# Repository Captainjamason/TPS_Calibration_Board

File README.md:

# TPS_Calibration_Board
WIP...          Copyright JPD/Davis Tuning, 2025.

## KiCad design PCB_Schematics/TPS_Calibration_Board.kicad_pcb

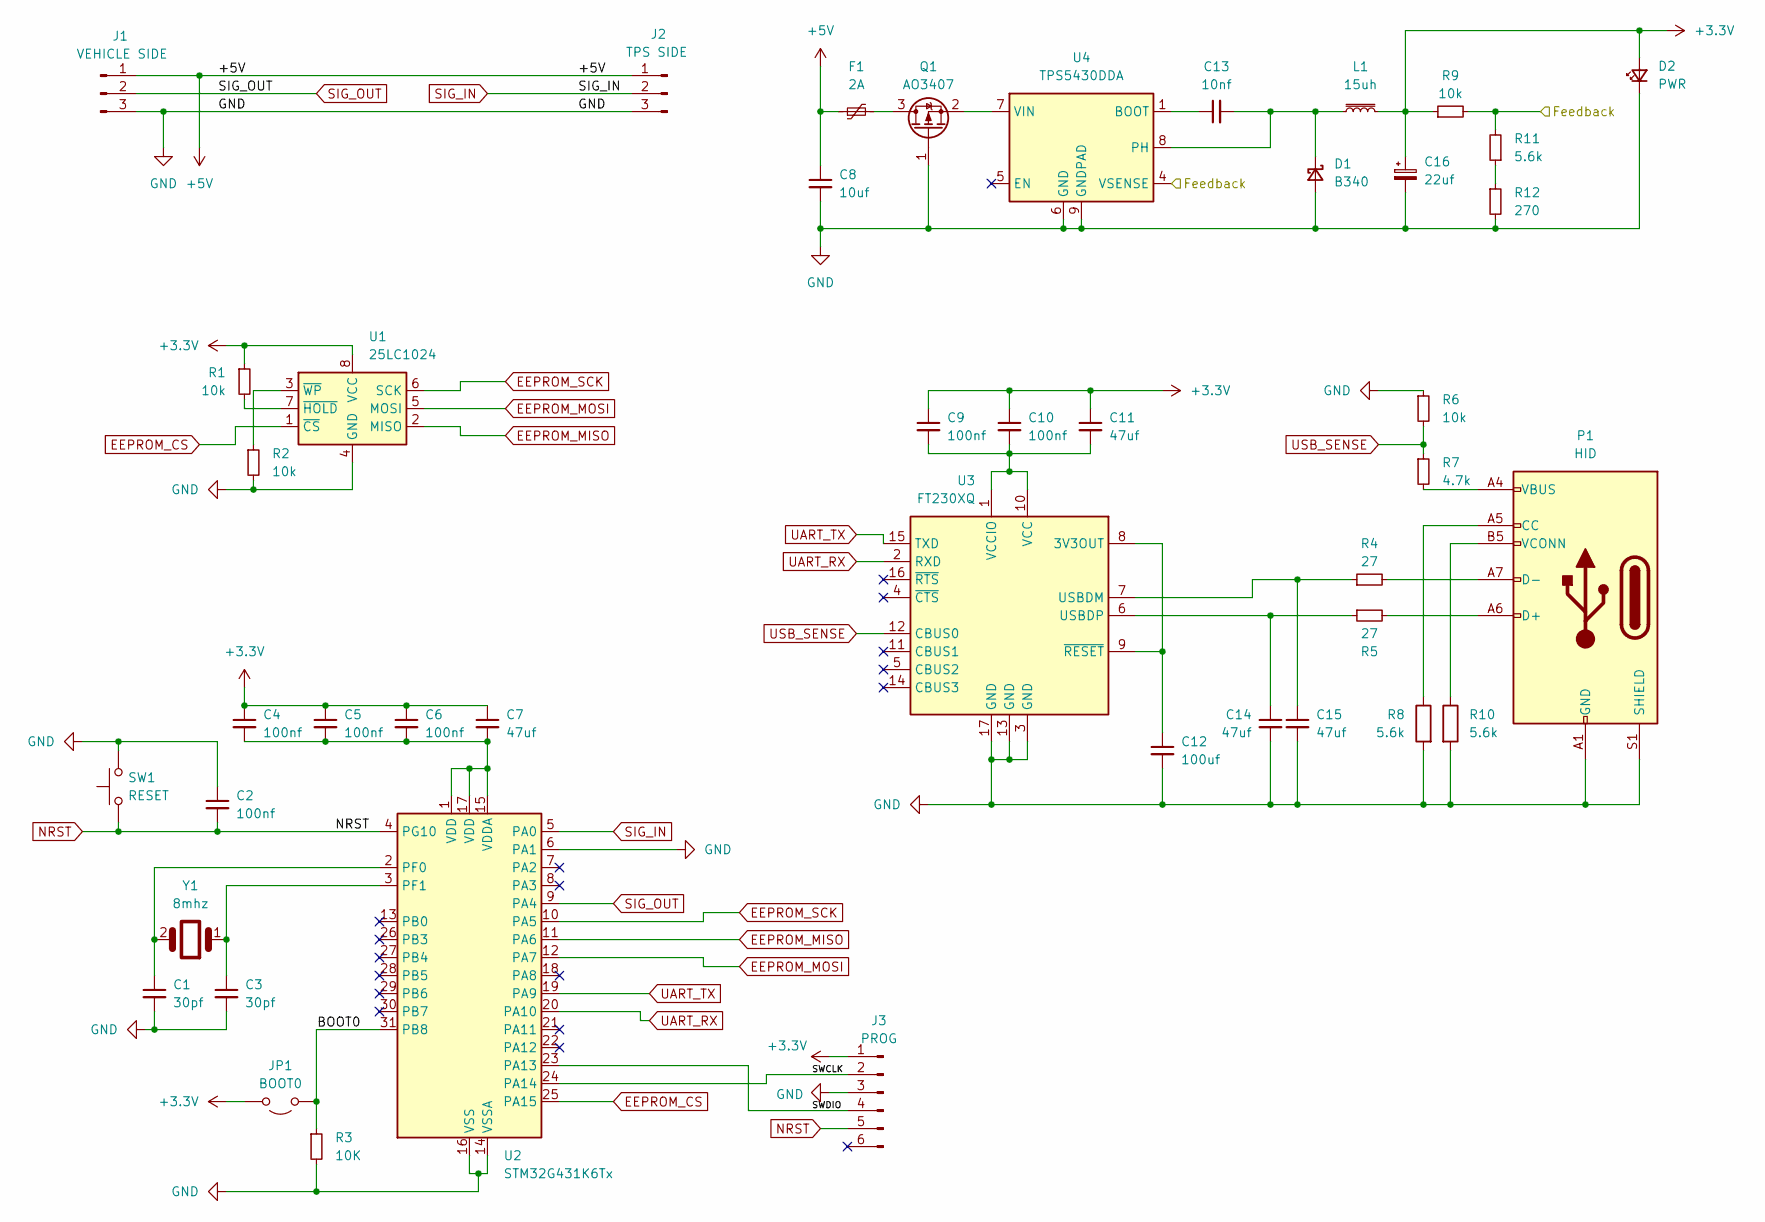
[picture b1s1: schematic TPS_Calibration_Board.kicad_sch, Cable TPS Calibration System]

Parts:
C1, C3: 30pf; C_0805_2012Metric_Pad1.18x1.45mm_HandSolder
C2, C4, C5, C6, C9, C10: 100nf; C_0805_2012Metric_Pad1.18x1.45mm_HandSolder
C7, C11, C14, C15: 47uf; C_0805_2012Metric_Pad1.18x1.45mm_HandSolder
C8: 10uf; C_0805_2012Metric_Pad1.18x1.45mm_HandSolder
C12: 100uf; C_0805_2012Metric_Pad1.18x1.45mm_HandSolder
C13: 10nf; C_0805_2012Metric_Pad1.18x1.45mm_HandSolder
C16: 22uf; C_0805_2012Metric_Pad1.18x1.45mm_HandSolder
D1: B340; D_SMC_Handsoldering
D2: PWR; LED_1206_3216Metric_Pad1.42x1.75mm_HandSolder
F1: 2A; Fuse_0805_2012Metric_Pad1.15x1.40mm_HandSolder
J1: VEHICLE SIDE; PinHeader_1x03_P2.54mm_Vertical
J2: TPS SIDE; PinHeader_1x03_P2.54mm_Vertical
J3: PROG; PinHeader_1x06_P2.54mm_Vertical
JP1: BOOT0; PinHeader_1x03_P2.54mm_Vertical
L1: 15uh; L_1210_3225Metric_Pad1.42x2.65mm_HandSolder
P1: HID; USB_C_Receptacle_Molex_105450-0101
Q1: AO3407; SOT-23
R1, R2, R6, R9: 10k; R_1206_3216Metric_Pad1.30x1.75mm_HandSolder
R3: 10K; R_1206_3216Metric_Pad1.30x1.75mm_HandSolder
R4, R5: 27; R_1206_3216Metric_Pad1.30x1.75mm_HandSolder
R7: 4.7k; R_1206_3216Metric_Pad1.30x1.75mm_HandSolder
R8, R10, R11: 5.6k; R_1206_3216Metric_Pad1.30x1.75mm_HandSolder
R12: 270; R_1206_3216Metric_Pad1.30x1.75mm_HandSolder
SW1: RESET; SW_SPST_B3S-1000
U1: 25LC1024; DIP-8_W7.62mm_Socket
U2: STM32G431K6Tx; LQFP-32_7x7mm_P0.8mm
U3: FT230XQ; QFN-16-1EP_4x4mm_P0.65mm_EP2.1x2.1mm
U4: TPS5430DDA; TI_SO-PowerPAD-8_ThermalVias
Y1: 8mhz; Crystal_HC49-4H_Vertical

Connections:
+3.3V: C4.1, C5.1, C6.1, C7.1, C9.1, C10.1, C11.1, C16.1, D2.2 (A), J3.1, JP1.2 (B), L1.2, R1.1, R9.1, U1.8 (VCC)
+5V: C8.1, F1.1, J1.1, J2.1
/BOOT0: JP1.1 (A), R3.1, U2.31 (PB8)
/Feedback: R9.2, R11.2, U4.4 (VSENSE)
/SWCLK: J3.2, U2.24 (PA14)
/SWDIO: J3.4, U2.23 (PA13)
EEPROM_CS: U1.1 (~CS), U2.25 (PA15)
EEPROM_MISO: U1.2 (MISO), U2.11 (PA6)
EEPROM_MOSI: U1.5 (MOSI), U2.12 (PA7)
EEPROM_SCK: U1.6 (SCK), U2.10 (PA5)
GND: C1.2, C2.1, C3.2, C8.2, C12.2, C14.2, C15.2, C16.2, D1.2 (A), D2.1 (K), J1.3, J2.3, J3.3, P1.A1 (GND), P1.A12 (GND), P1.B1 (GND), P1.B12 (GND), P1.S1 (SHIELD), Q1.1 (G), R2.2, R3.2, R6.1, R8.2, R10.2, R12.2, SW1.2, U1.4 (GND), U2.6 (PA1), U2.14 (VSSA), U2.16 (VSS), U2.32 (VSS), U3.3 (GND), U3.13 (GND), U3.17 (GND), U4.6 (GND), U4.9 (GNDPAD)
NRST: C2.2, J3.5, SW1.1, U2.4 (PG10)
unnamed: C13.2, D1.1 (K), L1.1, U4.8 (PH)
unnamed: P1.A5 (CC), R8.1
unnamed: P1.A6 (D+), R5.2
unnamed: P1.A7 (D-), R4.2
unnamed: P1.A4 (VBUS), P1.A9 (VBUS), P1.B4 (VBUS), P1.B9 (VBUS), R7.2
unnamed: P1.B5 (VCONN), R10.1
unnamed: F1.2, Q1.3 (D)
unnamed: Q1.2 (S), U4.7 (VIN)
unnamed: R11.1, R12.1
unnamed: R1.2, U1.7 (~HOLD)
unnamed: R2.1, U1.3 (~WP)
unnamed: C1.1, U2.2 (PF0), Y1.2
unnamed: C3.1, U2.3 (PF1), Y1.1
unnamed: C4.2, C5.2, C6.2, C7.2, U2.1 (VDD), U2.15 (VDDA), U2.17 (VDD)
unnamed: C12.1, U3.8 (3V3OUT), U3.9 (~RESET)
unnamed: C15.1, R4.1, U3.7 (USBDM)
unnamed: C14.1, R5.1, U3.6 (USBDP)
unnamed: C9.2, C10.2, C11.2, U3.1 (VCCIO), U3.10 (VCC)
unnamed: C13.1, U4.1 (BOOT)
SIG_IN: J2.2, U2.5 (PA0)
SIG_OUT: J1.2, U2.9 (PA4)
UART_RX: U2.20 (PA10), U3.2 (RXD)
UART_TX: U2.19 (PA9), U3.15 (TXD)
USB_SENSE: R6.2, R7.1, U3.12 (CBUS0)

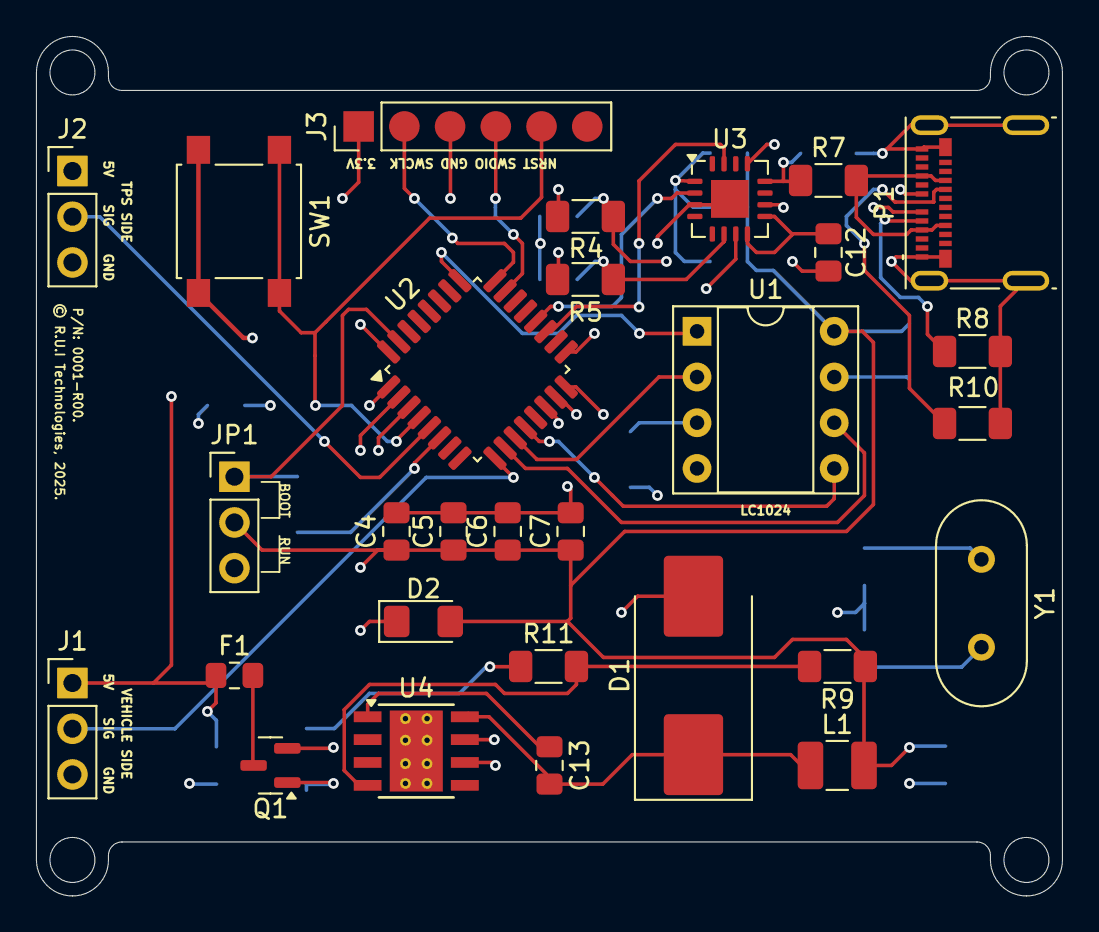
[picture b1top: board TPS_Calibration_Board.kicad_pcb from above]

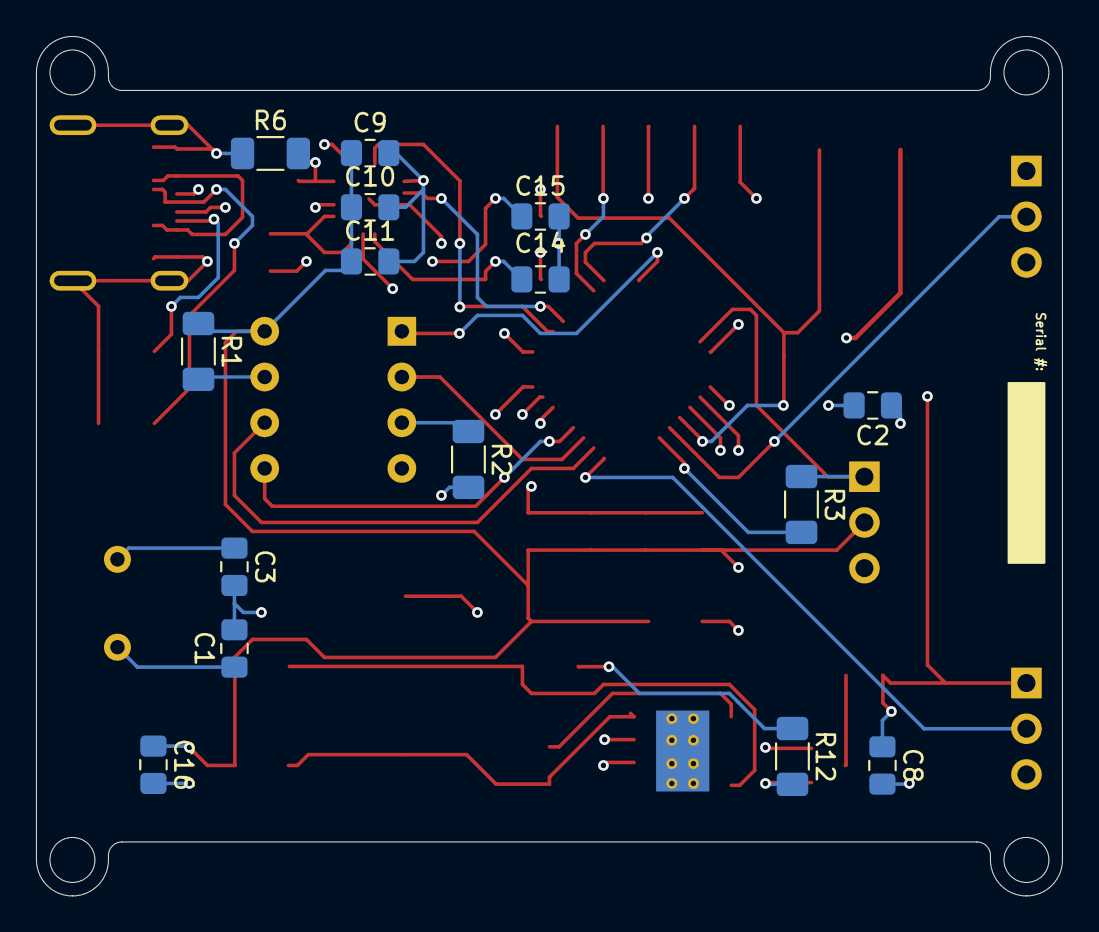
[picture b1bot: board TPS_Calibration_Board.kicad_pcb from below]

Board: 4 copper layers, 57.0 x 47.8 mm, 44 parts (15 on the bottom side), 36 nets.

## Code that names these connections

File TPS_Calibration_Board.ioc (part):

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Mcu.Name=STM32G431K(6-8-B)Tx
Mcu.Package=LQFP32
Mcu.UserName=STM32G431K6Tx
PA0.Mode=IN1-Differential
PA0.Signal=ADC1_IN1
PA1.Mode=IN1-Differential
PA1.Signal=ADC1_IN2
PA10.Mode=Asynchronous
PA10.Signal=USART1_RX
PA13.Signal=SYS_JTMS-SWDIO
PA14.Signal=SYS_JTCK-SWCLK
PA15.GPIOParameters=PinState,GPIO_Label
PA15.GPIO_Label=EEPROM_CS
PA15.PinState=GPIO_PIN_SET
PA15.Signal=GPIO_Output
PA4.Signal=COMP_DAC11_group
PA5.Mode=Full_Duplex_Master
PA5.Signal=SPI1_SCK
PA6.Mode=Full_Duplex_Master
PA6.Signal=SPI1_MISO
PA7.Mode=Full_Duplex_Master
PA7.Signal=SPI1_MOSI
PA9.Mode=Asynchronous
PA9.Signal=USART1_TX
RCC.HSE_VALUE=8000000
RCC.SYSCLKFreq_VALUE=16000000
board=custom

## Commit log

2025-05-29 Start of R00, Basic MX config.
2025-05-31 Finished board R00.
2025-06-01 Minor changes
2025-06-01 Basic Java Tuner project. Finished board, minor labeling required

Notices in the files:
PCB_Schematics/TPS_Calibration_Board.kicad_pcb:
© R.U.I Technologies, 2025.
